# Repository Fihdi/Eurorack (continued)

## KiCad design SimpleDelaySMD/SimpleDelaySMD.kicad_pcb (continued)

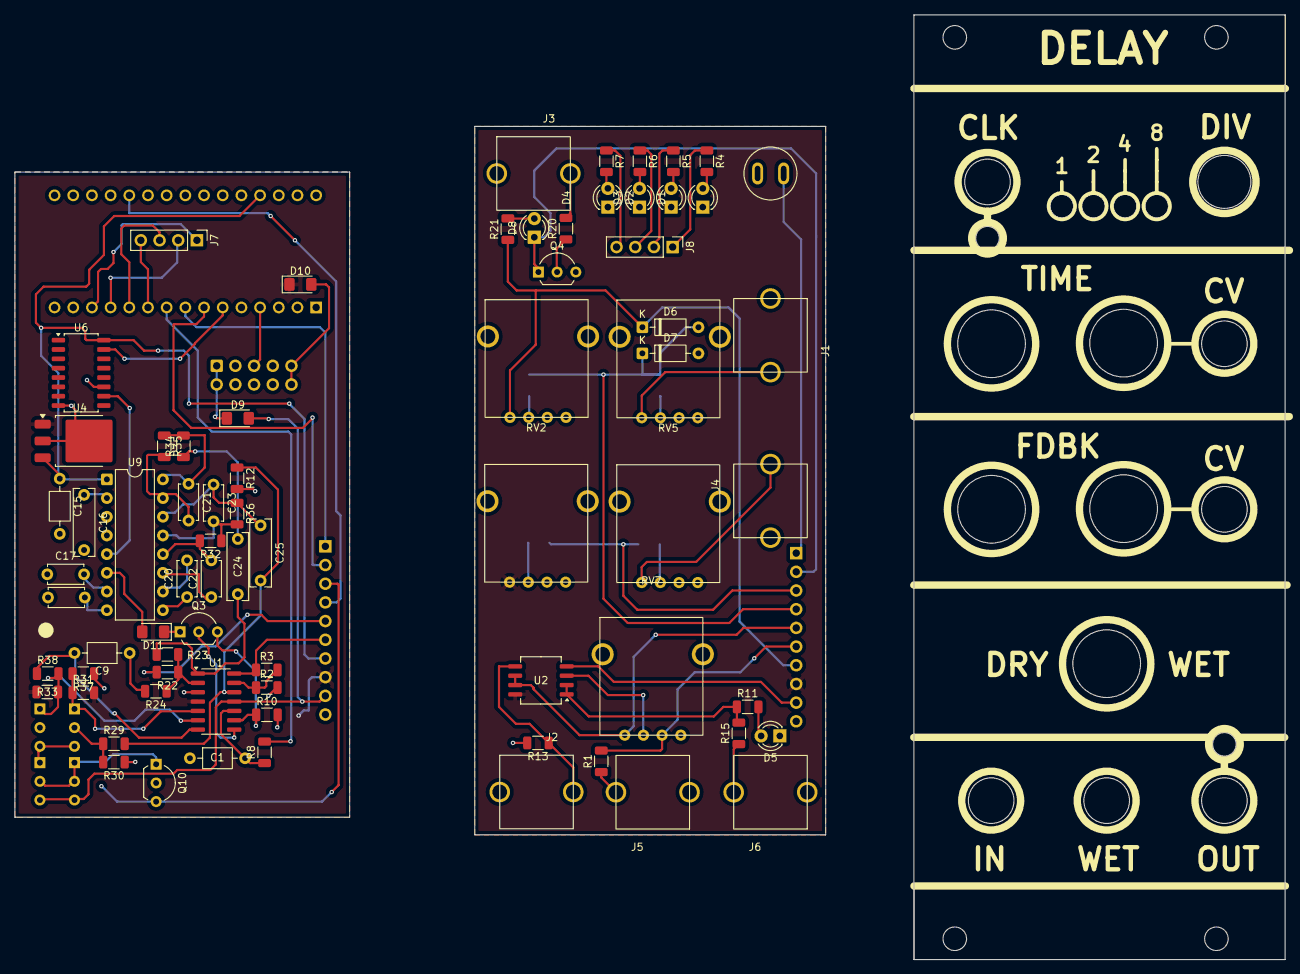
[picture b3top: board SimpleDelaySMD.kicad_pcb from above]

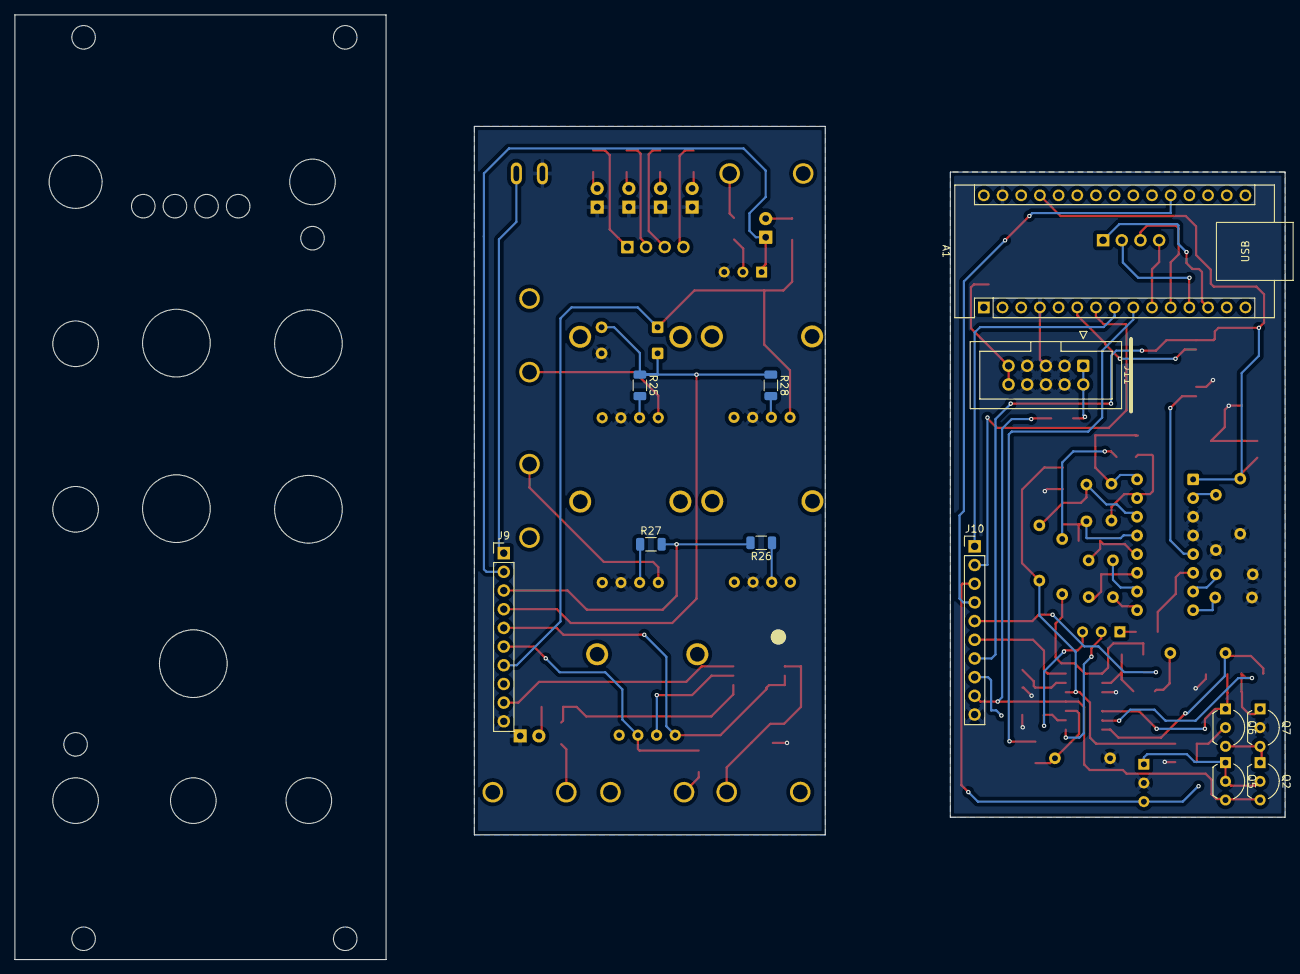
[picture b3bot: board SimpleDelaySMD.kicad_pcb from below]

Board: 2 copper layers, 172.6 x 128.4 mm, 85 parts (12 on the bottom side), 66 nets.

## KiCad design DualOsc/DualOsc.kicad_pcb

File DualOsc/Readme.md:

# 18hp Dual VCO module

Two triangle core VCOs with volt per octave tracking, FM, Synchronization and PWM. Both VCOs are identical and can be used independantely. The middle section allows for modulation (AM, FM and synchronization) from the left VCO to the right VCO and can be switched on or off via switches. The strength of this modulation is controllable via the AMT knob and a control voltage and is indicated by the arrow LED. Four trimmers at the back of the mainboard are used to tune the volt per octave responses and the sine shapers. 

This module was meant to replace my old VCO and I have decided to build this project using SMD components to save space and to test the in-house PCB assembly by [PCBWay](https://www.pcbway.com/). It was great to receive a fully assembled board without having to solder it for hours, which can be very tedious when using SMD components. The soldering was perfect out of the box and it allowed me to solder in the last THT components and to tune the module. The front panel is also made of FR4 with white silkscreen and a glossy black finish. I received great help from their support regarding the formatting of the BOM, which they used to source the materials and to assemble my PCB.

Here is a small demo: https://youtu.be/suYPOwo4L5c

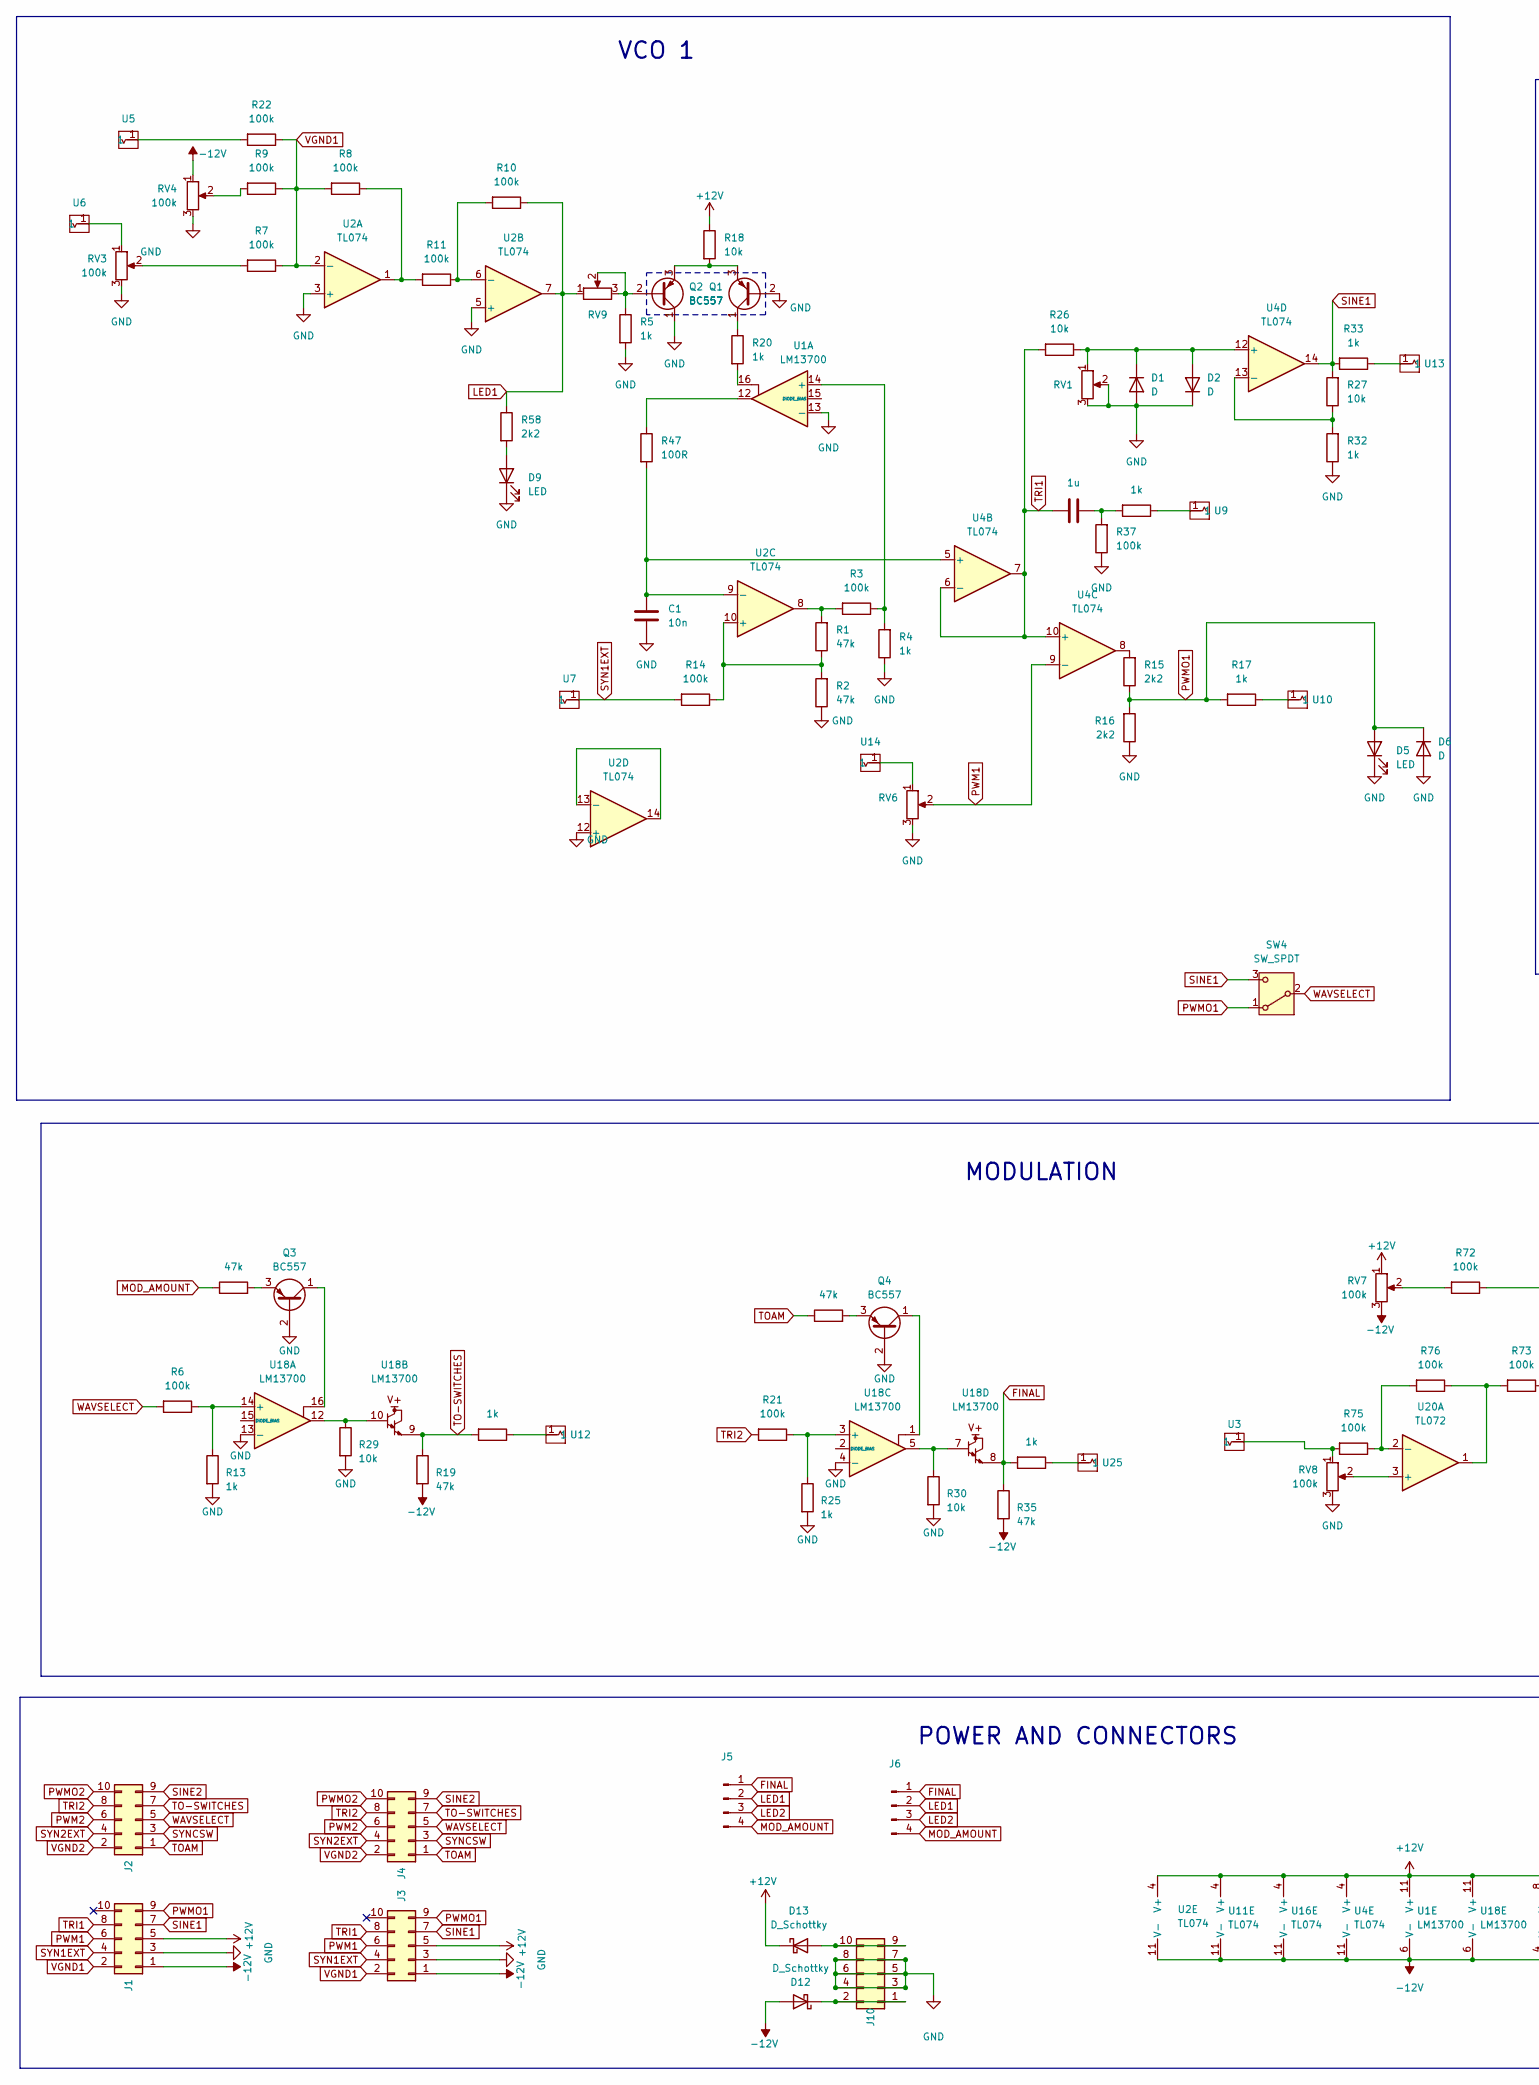
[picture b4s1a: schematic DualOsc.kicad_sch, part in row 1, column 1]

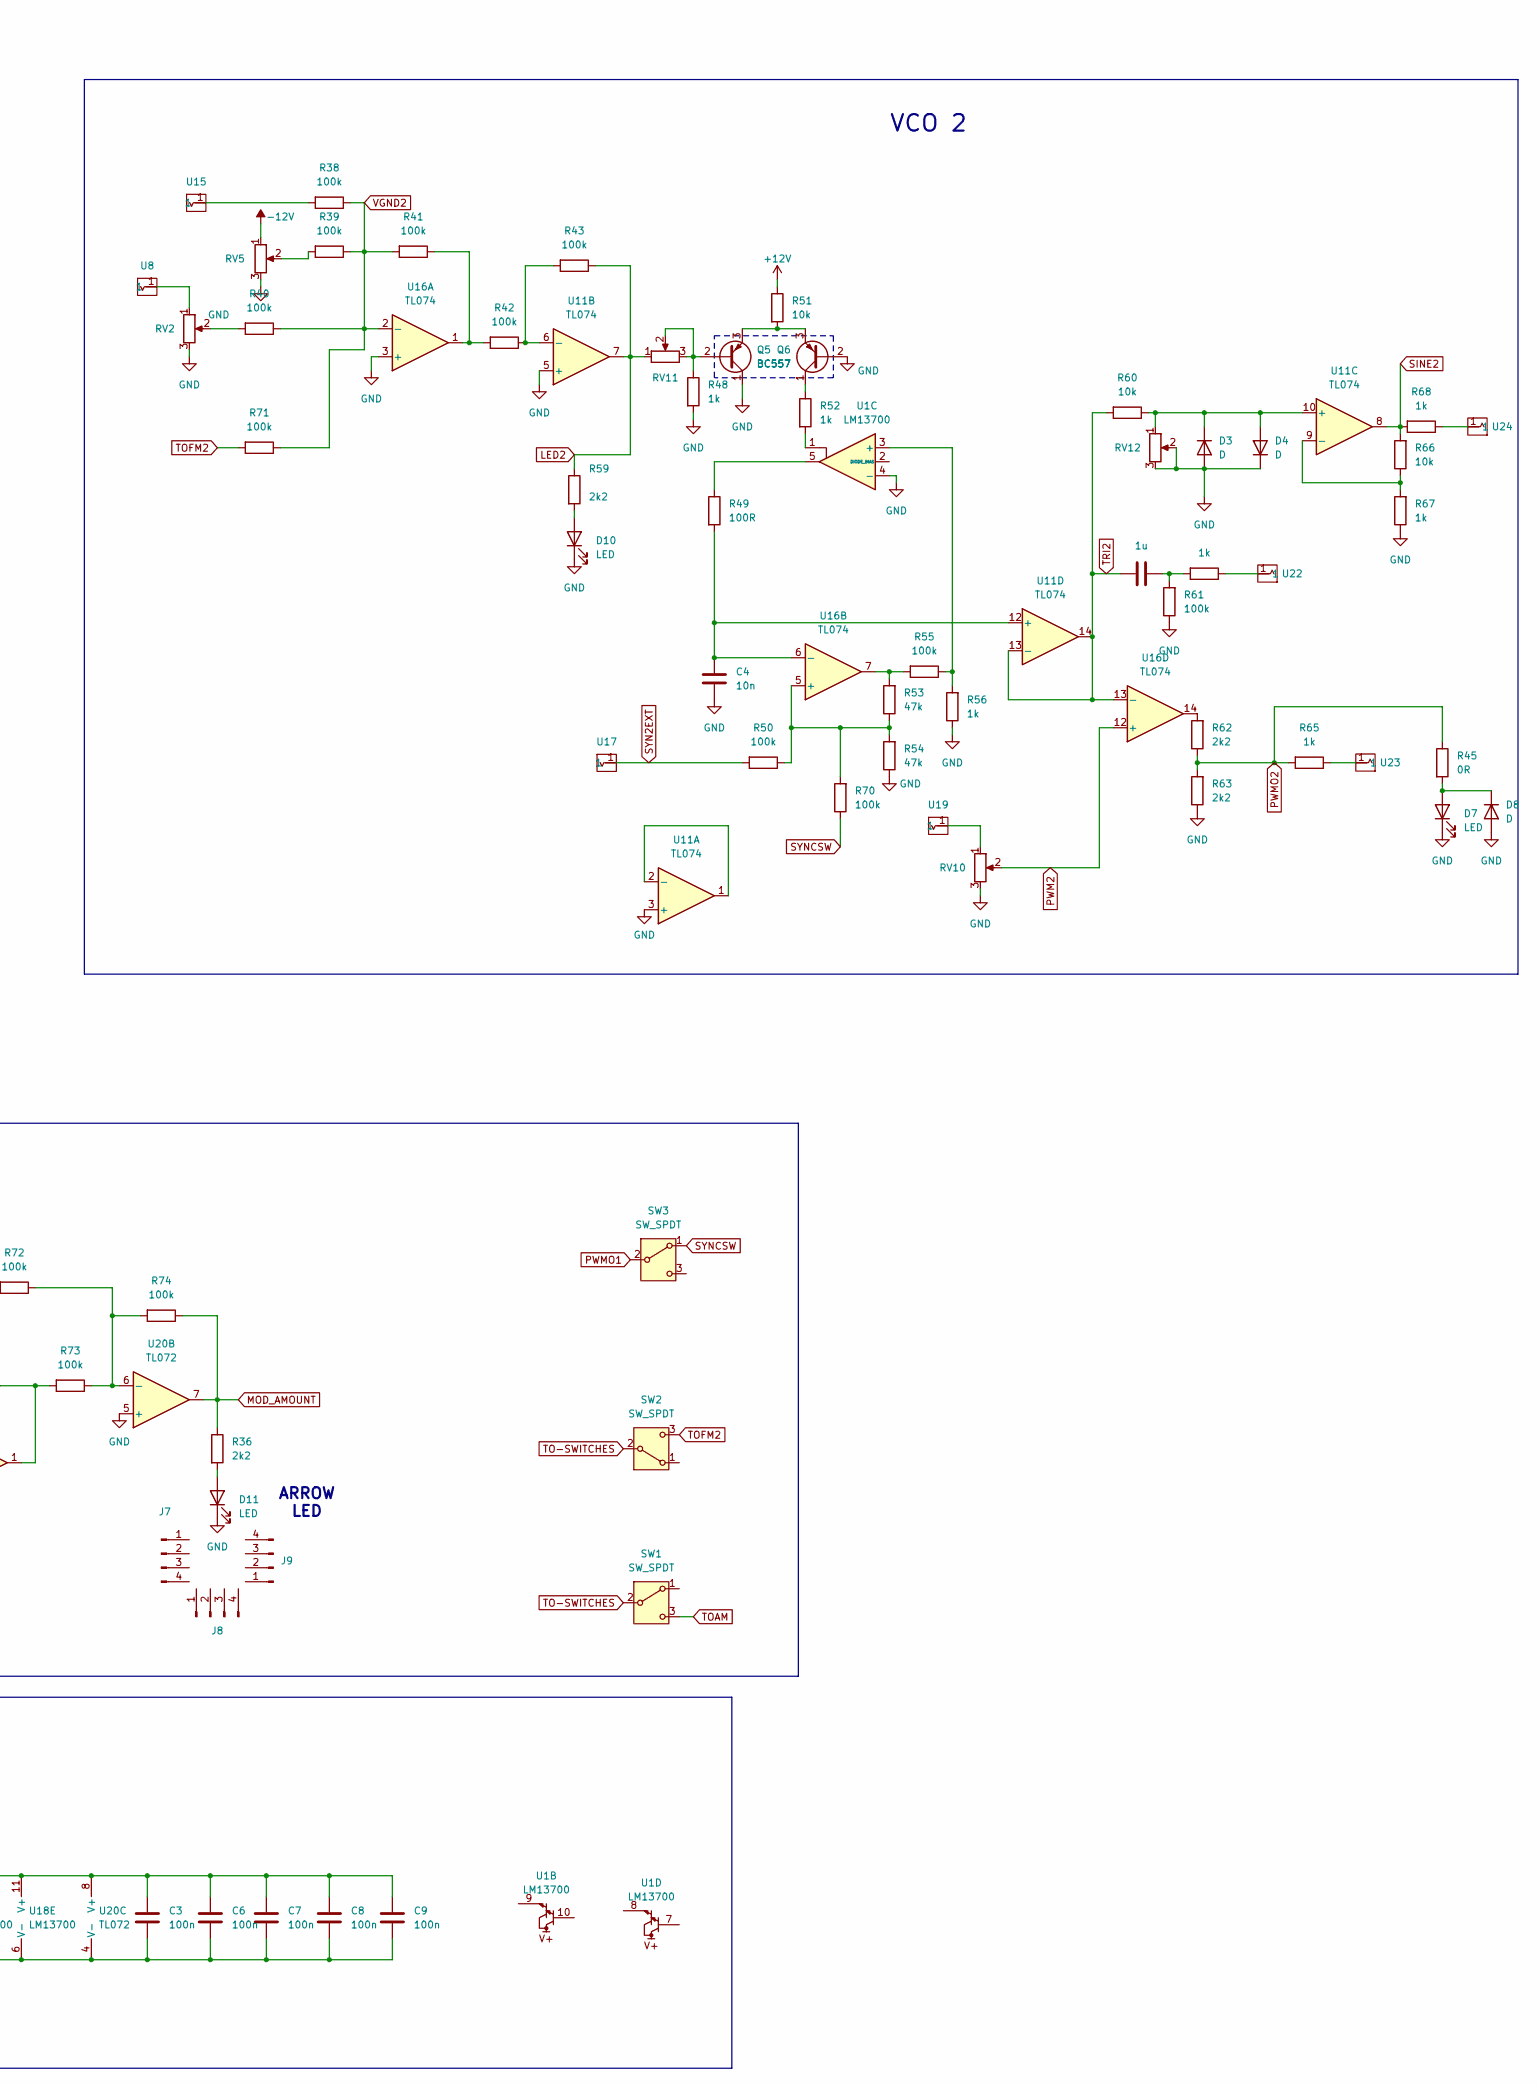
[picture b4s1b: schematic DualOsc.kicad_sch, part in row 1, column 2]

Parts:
C1, C4: 10n; C_Rect_L7.0mm_W2.5mm_P5.00mm
C2, C5: 1u; C_Rect_L7.0mm_W2.5mm_P5.00mm
C3, C6, C7, C8, C9: 100n; C_1206_3216Metric
D1, D2, D3, D4, D6, D8: D; D_SOD-323_HandSoldering
D5, D7, D9, D10, D11: LED; LED_D3.0mm
D12, D13: D_Schottky; D_SOD-323_HandSoldering
J1, J2, J3, J4: Conn_02x05_Odd_Even; PinHeader_2x05_P2.54mm_Vertical
J5, J6, J7, J8, J9: Conn_01x04_Pin; PinSocket_1x04_P2.54mm_Vertical
J10: Conn_02x05_Odd_Even; IDC-Header_2x05_P2.54mm_Vertical
Q1, Q2, Q3, Q4, Q5, Q6: BC557; TO-92L_Inline_Wide
R1, R2, R19, R28, R35, R53, R54, R83: 47k; R_1206_3216Metric
R3, R6, R7, R8, R9, R10, R11, R14, R21, R22, R37, R38, R39, R40, R41, R42, R43, R50, R55, R61, R70, R71, R72, R73, R74, R75, R76: 100k; R_1206_3216Metric
R4, R5, R12, R13, R17, R20, R25, R31, R32, R33, R48, R52, R56, R64, R65, R67, R68, R69: 1k; R_1206_3216Metric
R15, R16, R36, R58, R59, R62, R63: 2k2; R_1206_3216Metric
R18, R26, R27, R29, R30, R51, R60, R66: 10k; R_1206_3216Metric
R45: 0R; R_1206_3216Metric
R47, R49: 100R; R_1206_3216Metric
RV1, RV12: 4k7; Potentiometer_ACP_CA9-H5_Horizontal
RV2, RV3, RV4, RV5, RV7, RV8, RV10: 100k; AlpsPot
RV6: R_Potentiometer; AlpsPot
RV9, RV11: 47k; Potentiometer_ACP_CA9-H5_Horizontal
SW1, SW2, SW3, SW4: SW_SPDT; Switch
U1, U18: LM13700; SOIC-16_3.9x9.9mm_P1.27mm
U2, U4, U11, U16: TL074; SOIC-14_3.9x8.7mm_P1.27mm
U3, U5, U6, U7, U8, U9, U10, U12, U13, U14, U15, U17, U19, U22, U23, U24, U25: Aux_flush; 3mm5 Mono Aux
U20: TL072; SOIC-8_3.9x4.9mm_P1.27mm

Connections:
+12V: C3.1, C6.1, C7.1, C8.1, C9.1, D13.1 (K), J1.5, J3.5, R18.1, R51.1, RV7.1, U1.11 (V+), U2.4 (V+), U4.4 (V+), U11.4 (V+), U16.4 (V+), U18.11 (V+), U20.8 (V+)
-12V: C3.2, C6.2, C7.2, C8.2, C9.2, D12.2 (A), J1.1, J3.1, R19.2, R35.2, RV4.1, RV5.1, RV7.3, U1.6 (V-), U2.11 (V-), U4.11 (V-), U11.11 (V-), U16.11 (V-), U18.6 (V-), U20.4 (V-)
FINAL: J5.1, J6.1, R35.1, R69.2, U18.8
GND: C1.2, C4.2, D1.2 (A), D2.1 (K), D3.2 (A), D4.1 (K), D5.1 (K), D6.2 (A), D7.1 (K), D8.2 (A), D9.1 (K), D10.1 (K), D11.1 (K), J1.3, J3.3, J10.3, J10.4, J10.5, J10.6, J10.7, J10.8, Q1.2 (B), Q2.1 (C), Q3.2 (B), Q4.2 (B), Q5.1 (C), Q6.2 (B), R2.1, R4.1, R5.2, R13.2, R16.1, R25.2, R29.2, R30.2, R32.1, R37.1, R48.2, R54.1, R56.1, R61.1, R63.1, R67.1, RV1.2, RV1.3, RV2.3, RV3.3, RV4.3, RV5.3, RV6.3, RV8.3, RV10.3, RV12.2, RV12.3, U1.4 (-), U1.13 (-), U2.3 (+), U2.5 (+), U2.12 (+), U11.3 (+), U11.5 (+), U16.3 (+), U18.4 (-), U18.13 (-), U20.5 (+)
LED1: J5.2, J6.2, R10.1, R58.1, RV9.1, U2.7
LED2: J5.3, J6.3, R43.1, R59.1, RV11.1, U11.7
MOD_AMOUNT: J5.4, J6.4, R36.1, R74.1, R83.1, U20.7
unnamed: C2.2, R12.2, R37.2
unnamed: C5.2, R61.2, R64.2
unnamed: D1.1 (K), D2.2 (A), R26.1, RV1.1, U4.12 (+)
unnamed: D3.1 (K), D4.2 (A), R60.1, RV12.1, U11.10 (+)
unnamed: D7.2 (A), D8.1 (K), R45.2
unnamed: D9.2 (A), R58.2
unnamed: D10.2 (A), R59.2
unnamed: D11.2 (A), R36.2
unnamed: D12.1 (K), J10.1, J10.2
unnamed: D13.2 (A), J10.9, J10.10
unnamed: Q1.1 (C), R20.1
unnamed: Q1.3 (E), Q2.3 (E), R18.2
unnamed: Q2.2 (B), R5.1, RV9.2, RV9.3
unnamed: Q3.1 (C), U18.16
unnamed: Q3.3 (E), R83.2
unnamed: Q4.1 (C), U18.1
unnamed: Q4.3 (E), R28.2
unnamed: Q5.2 (B), R48.1, RV11.2, RV11.3
unnamed: Q5.3 (E), Q6.3 (E), R51.2
unnamed: Q6.1 (C), R52.1
unnamed: R1.2, R3.2, U2.8
unnamed: R7.2, RV3.2
unnamed: R9.2, RV4.2
unnamed: R8.1, R11.2, U2.1
unnamed: R12.1, U9.1
unnamed: R15.2, U4.8
unnamed: R17.1, U10.1
unnamed: R20.2, U1.16
unnamed: R22.2, U5.1
unnamed: R29.1, U18.10, U18.12
unnamed: R30.1, U18.5, U18.7
unnamed: R31.1, U12.1
unnamed: R33.1, U13.1
unnamed: R38.2, U15.1
unnamed: R39.2, RV5.2
unnamed: R40.2, RV2.2
unnamed: R41.1, R42.2, U16.1
unnamed: R47.1, U1.12
unnamed: R49.1, U1.5
unnamed: R52.2, U1.1
unnamed: R53.2, R55.2, U16.7
unnamed: R62.2, U16.14
unnamed: R64.1, U22.1
unnamed: R65.1, U23.1
unnamed: R68.1, U24.1
unnamed: R69.1, U25.1
unnamed: R72.2, RV7.2
unnamed: R73.2, R76.1, U20.1
unnamed: R75.2, RV8.1, U3.1
unnamed: RV2.1, U8.1
unnamed: RV3.1, U6.1
unnamed: RV6.1, U14.1
unnamed: RV10.1, U19.1
unnamed: R3.1, R4.2, U1.14 (+)
unnamed: R55.1, R56.2, U1.3 (+)
unnamed: R10.2, R11.1, U2.6 (-)
unnamed: R1.1, R2.2, R14.1, U2.10 (+)
unnamed: C1.1, R47.2, U2.9 (-), U4.5 (+)
unnamed: U2.13 (-), U2.14
unnamed: R27.1, R32.2, U4.13 (-)
unnamed: U11.1, U11.2 (-)
unnamed: R42.1, R43.2, U11.6 (-)
unnamed: R66.1, R67.2, U11.9 (-)
unnamed: C4.1, R49.2, U11.12 (+), U16.6 (-)
unnamed: R50.1, R53.1, R54.2, R70.2, U16.5 (+)
unnamed: R6.1, R13.1, U18.14 (+)
unnamed: R21.1, R25.1, U18.3 (+)
unnamed: RV8.2, U20.3 (+)
unnamed: R75.1, R76.2, U20.2 (-)
unnamed: R72.1, R73.1, R74.2, U20.6 (-)
PWM1: J1.6, J3.6, RV6.2, U4.9 (-)
PWM2: J2.6, J4.6, RV10.2, U16.12 (+)
PWMO1: D5.2 (A), D6.1 (K), J1.9, J3.9, R15.1, R16.2, R17.2, SW3.2 (B), SW4.1 (A)
PWMO2: J2.10, J4.10, R45.1, R62.1, R63.2, R65.2
SINE1: J1.7, J3.7, R27.2, R33.2, SW4.3 (C), U4.14
SINE2: J2.9, J4.9, R66.2, R68.2, U11.8
SYN1EXT: J1.4, J3.4, R14.2, U7.1
SYN2EXT: J2.4, J4.4, R50.2, U17.1
SYNCSW: J2.3, J4.3, R70.1, SW3.1 (A)
TO-SWITCHES: J2.7, J4.7, R19.1, R31.2, SW1.2 (B), SW2.2 (B), U18.9
TOAM: J2.1, J4.1, R28.1, SW1.3 (C)
TOFM2: R71.2, SW2.3 (C)
TRI1: C2.1, J1.8, J3.8, R26.2, U4.6 (-), U4.7, U4.10 (+)
TRI2: C5.1, J2.8, J4.8, R21.2, R60.2, U11.13 (-), U11.14, U16.13 (-)
VGND1: J1.2, J3.2, R7.1, R8.2, R9.1, R22.1, U2.2 (-)
VGND2: J2.2, J4.2, R38.1, R39.1, R40.1, R41.2, R71.1, U16.2 (-)
WAVSELECT: J2.5, J4.5, R6.2, SW4.2 (B)

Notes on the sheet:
MODULATION
VCO 1
ARROW LED
POWER AND CONNECTORS
VCO 2

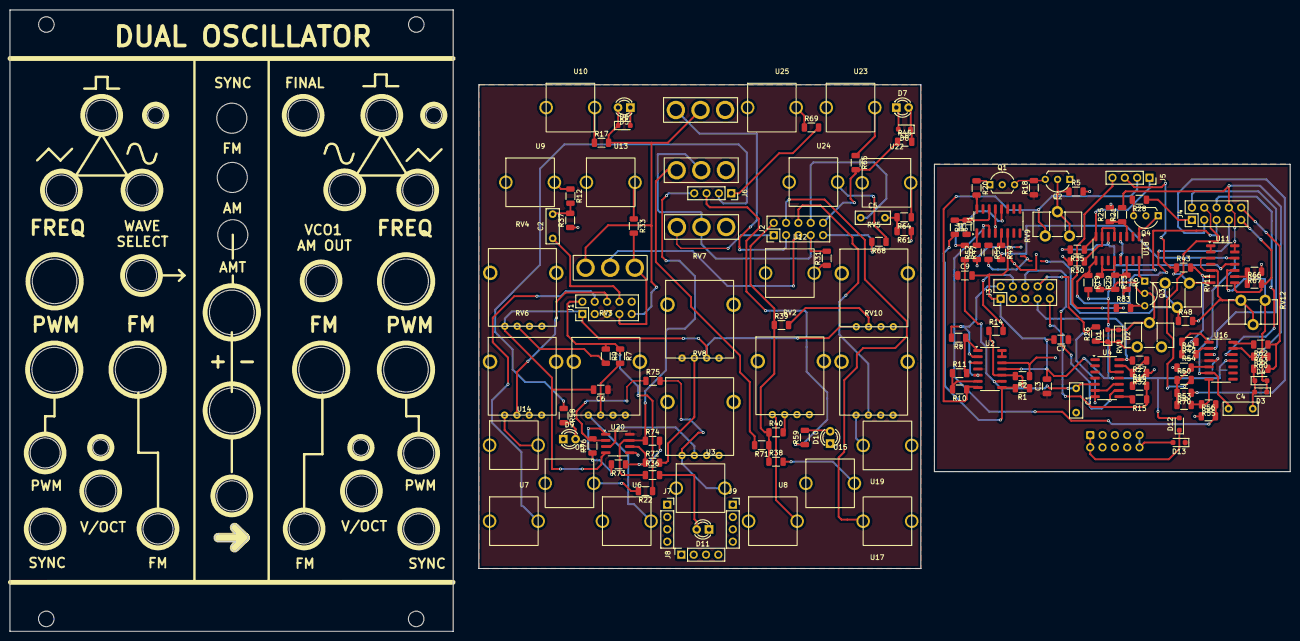
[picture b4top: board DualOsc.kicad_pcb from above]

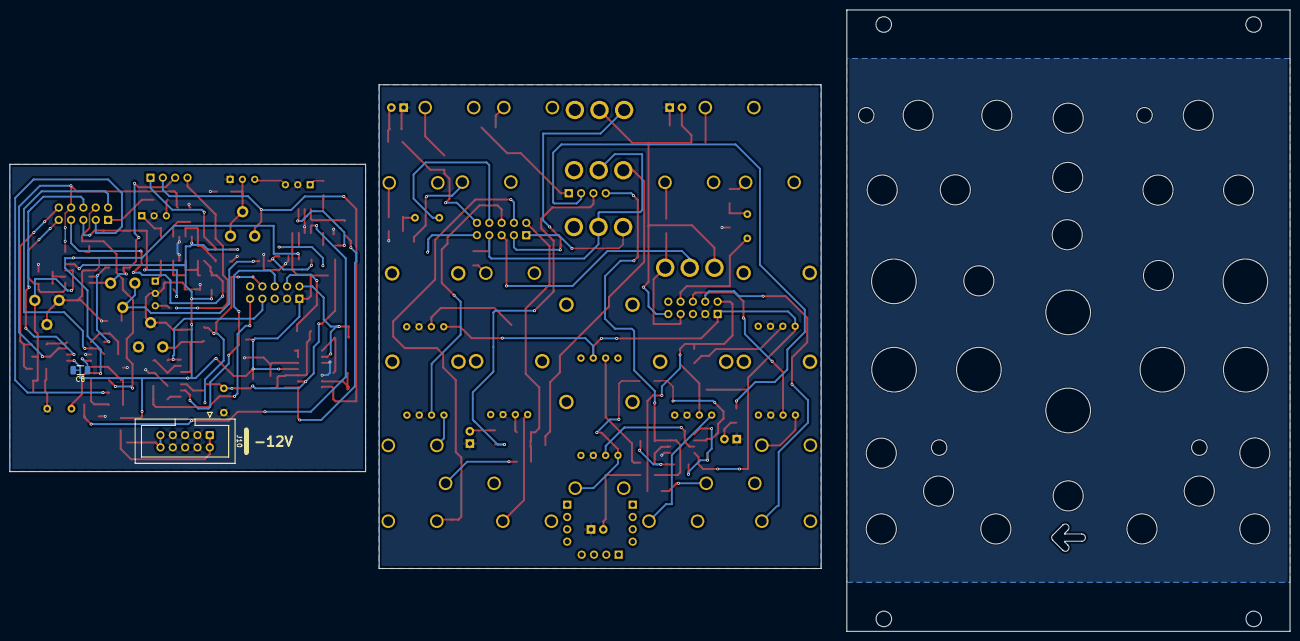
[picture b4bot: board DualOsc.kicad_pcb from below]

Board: 2 copper layers, 263.7 x 128.0 mm, 147 parts (2 on the bottom side), 92 nets.

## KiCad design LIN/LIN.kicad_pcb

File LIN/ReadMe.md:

# 4hp Line Input / VCA 

LIN is a 4hp Line Input module allowing you to take a line level signal from eg. a laptop, mp3 player, mobile phone etc. and boost it to Eurorack level. The volume is controlled by a VCA, which allows you to control the volume, or chop up the incoming audio signal. You can also distort existing eurorack signal by boosting the signal until it clips.

The module that you see in the picture above is the finished product using circuit boards that were fabricated by PCBWay. It is my smallest (slimmest) module so far and as always, they have excellent build quality! I used the "Black" option for the soldermask and the surface has very deep and glossy black finish, which looks amazing.

[Visit PCBWay](https://www.pcbway.com/) The website is intuitive and easy to use, just upload the gerber and drill files as a .zip-file, tick the options such as base material, board width, my favorite feature: separate colors for the soldermask and silkscreen, surface finish etc. With multiple options for payment and fast delivery fast times I was able to put the entire project together in less than one month.

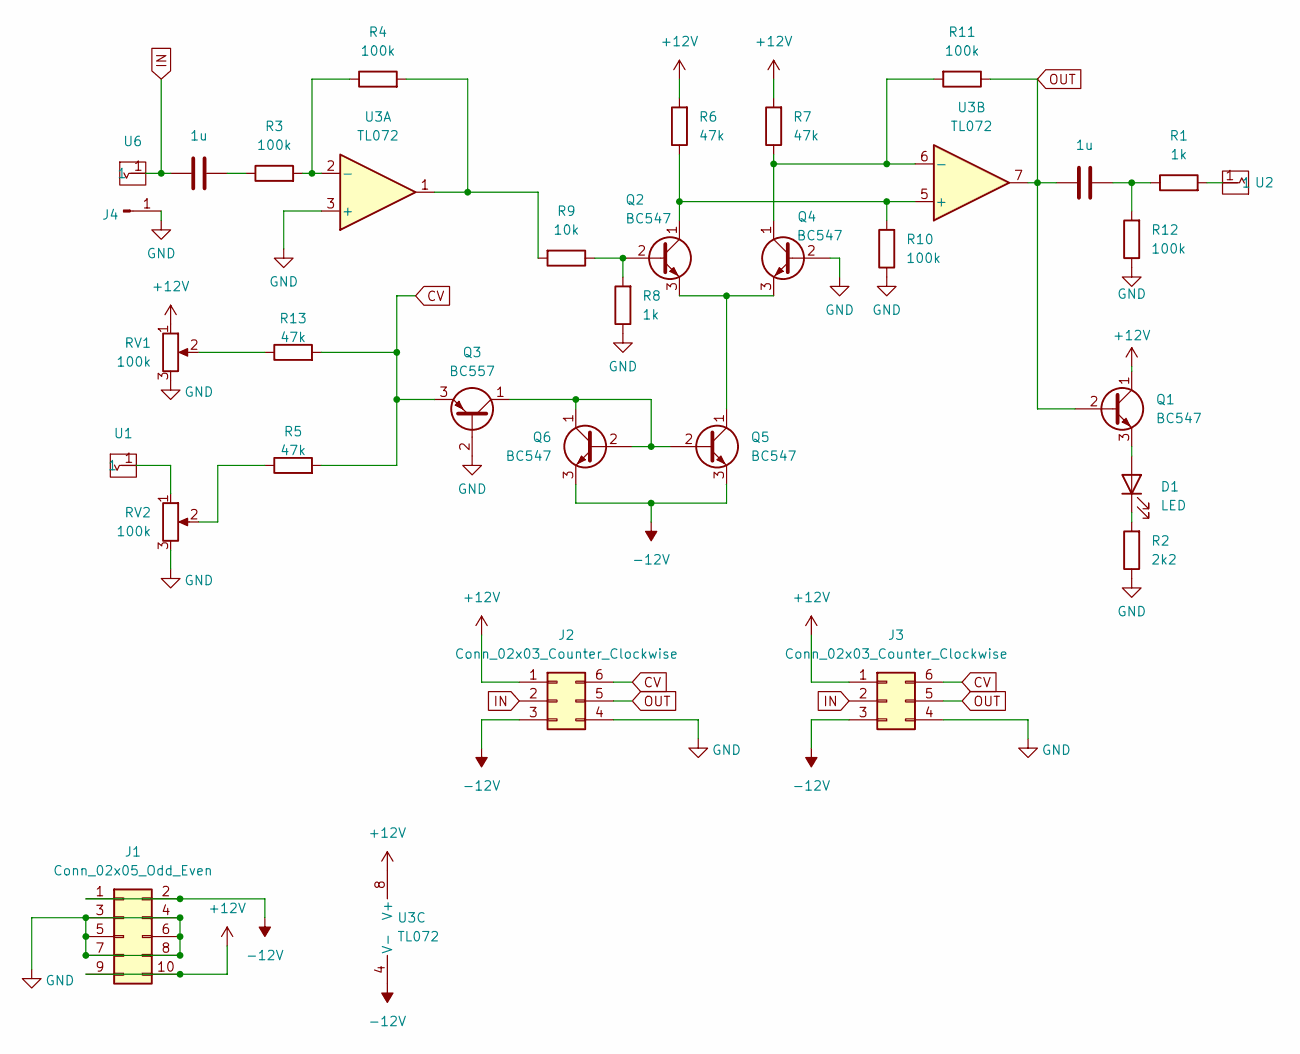
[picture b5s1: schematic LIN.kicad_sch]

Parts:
C1, C9: 1u; C_Axial_L3.8mm_D2.6mm_P7.50mm_Horizontal
D1: LED; LED_D5.0mm
J1: Conn_02x05_Odd_Even; IDC-Header_2x05_P2.54mm_Vertical
J2, J3: Conn_02x03_Counter_Clockwise; PinHeader_2x03_P2.54mm_Vertical
J4: Conn_01x01_Pin; PinSocket_1x01_P2.54mm_Vertical
Q1, Q2, Q4, Q5, Q6: BC547; TO-92L_Wide
Q3: BC557; TO-92L_Inline_Wide
R1, R8: 1k; R_Axial_DIN0207_L6.3mm_D2.5mm_P7.62mm_Horizontal
R2: 2k2; R_Axial_DIN0207_L6.3mm_D2.5mm_P7.62mm_Horizontal
R3, R4, R10, R11, R12: 100k; R_Axial_DIN0207_L6.3mm_D2.5mm_P7.62mm_Horizontal
R5, R6, R7, R13: 47k; R_Axial_DIN0207_L6.3mm_D2.5mm_P7.62mm_Horizontal
R9: 10k; R_Axial_DIN0207_L6.3mm_D2.5mm_P7.62mm_Horizontal
RV1, RV2: 100k; AlpsPot
U1, U2, U6: Aux_flush; 3mm5 Mono Aux
U3: TL072; DIP-8_W7.62mm

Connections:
+12V: J1.9, J1.10, J2.1, J3.1, Q1.1 (C), R6.2, R7.2, RV1.1, U3.8 (V+)
-12V: J1.1, J1.2, J2.3, J3.3, Q5.3 (E), Q6.3 (E), U3.4 (V-)
CV: J2.6, J3.6, Q3.3 (E), R5.2, R13.2
GND: J1.3, J1.4, J1.5, J1.6, J1.7, J1.8, J2.4, J3.4, J4.1, Q3.2 (B), Q4.2 (B), R2.1, R8.1, R10.1, R12.1, RV1.3, RV2.3, U3.3 (+)
IN: C1.2, J2.2, J3.2, U6.1
unnamed: C1.1, R3.1
unnamed: C9.1, R1.1, R12.2
unnamed: D1.2 (A), Q1.3 (E)
unnamed: D1.1 (K), R2.2
unnamed: Q2.2 (B), R8.2, R9.1
unnamed: Q2.1 (C), R6.1, R10.2, U3.5 (+)
unnamed: Q2.3 (E), Q4.3 (E), Q5.1 (C)
unnamed: Q3.1 (C), Q5.2 (B), Q6.1 (C), Q6.2 (B)
unnamed: Q4.1 (C), R7.1, R11.2, U3.6 (-)
unnamed: R1.2, U2.1
unnamed: R4.2, R9.2, U3.1
unnamed: R5.1, RV2.2
unnamed: R13.1, RV1.2
unnamed: RV2.1, U1.1
unnamed: R3.2, R4.1, U3.2 (-)
OUT: C9.2, J2.5, J3.5, Q1.2 (B), R11.1, U3.7

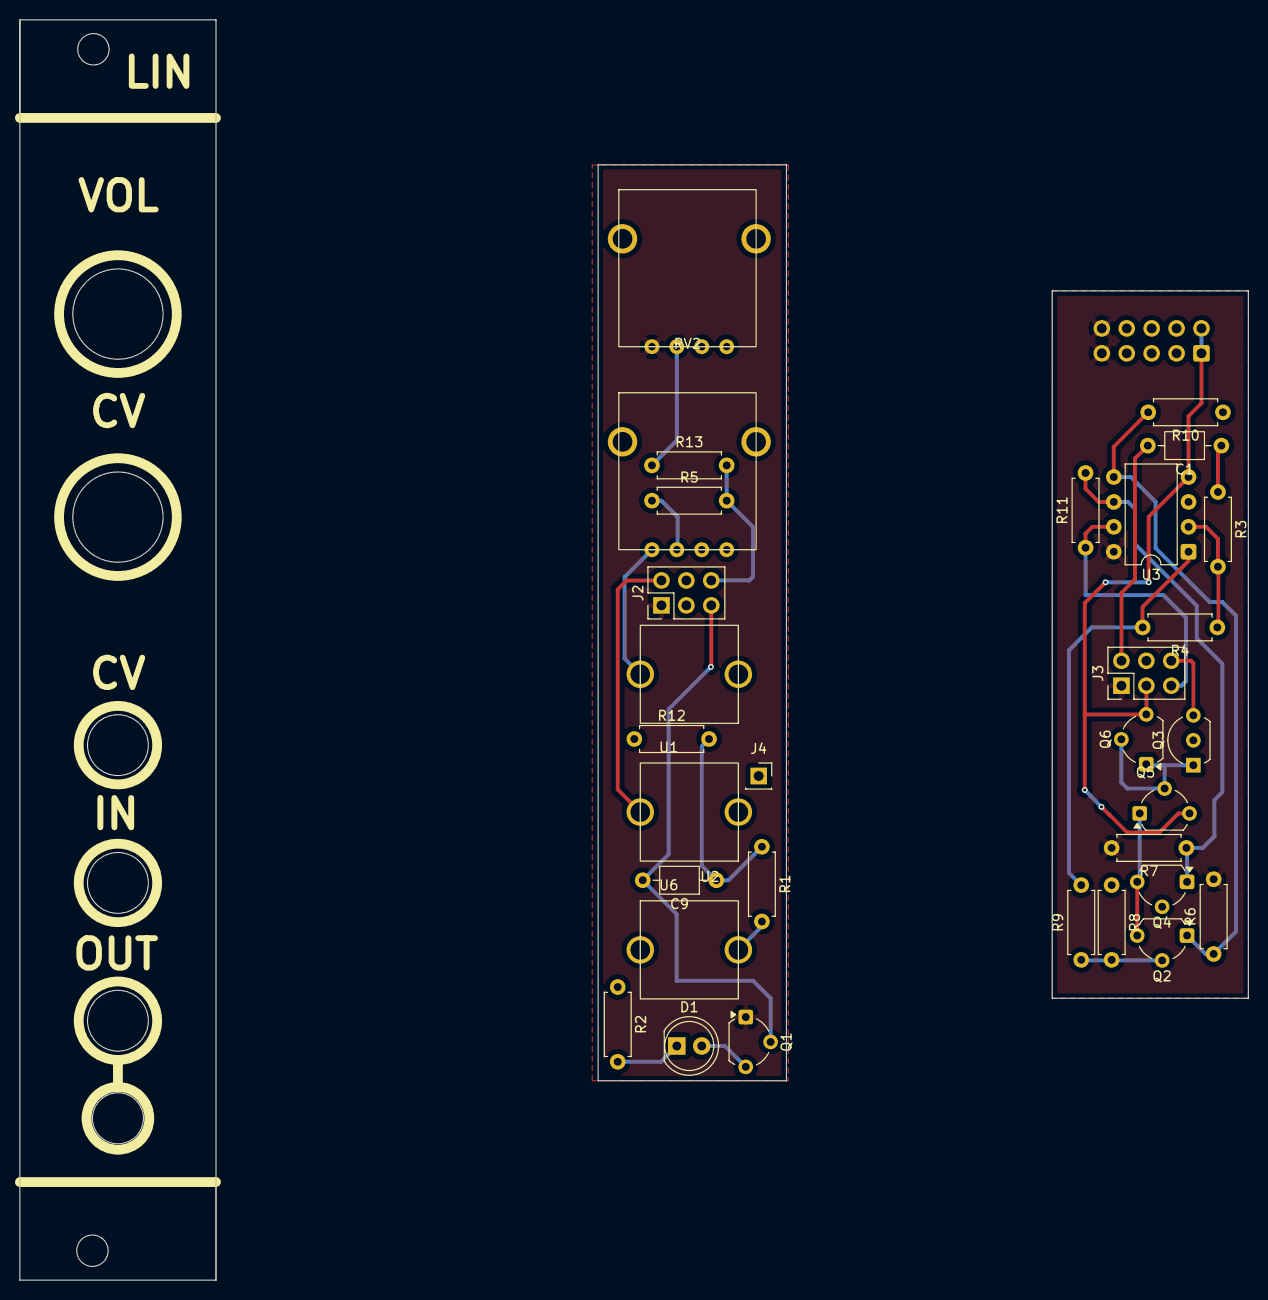
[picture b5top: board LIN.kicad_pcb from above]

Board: 2 copper layers, 125.3 x 128.5 mm, 32 parts (1 on the bottom side), 21 nets.

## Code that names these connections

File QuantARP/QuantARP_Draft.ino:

/*

Code by Fihdi

Matrix Keypad values:

13 = no key

col 1, 2, 3, 4
_________________
| 1 | 2 | 3 | 4 | row1 
_________________
| 5 | 6 | 7 | 8 | row2
_________________
| 9 | 10| 11| 12| row3
_________________

Scale:
col 1, 2, 3, 4
_________________
| C | C#| D | D#| row1 
_________________
| E | F | F#| G | row2
_________________
| G#| A | A#| B | row3
_________________

*/


#include "TCA9555.h"

#define TRG 9  //TRG Input Pin
#define CVIN A1   //CV Input Pin
#define ARP 5   //ARP Input Pin

#define CVOUT 10   //CV Output Pin
#define AUD 11  //Audio Output Pin

//Matrix Keypad Pins
#define ROW1 6
#define ROW2 7
#define ROW3 8
#define COL1 3
#define COL2 2
#define COL3 4
#define COL4 5

//LED Pins 
TCA9535 TCA(0x20);
#define LED1 1
#define LED2 2
#define LED3 3
#define LED4 4
#define LED5 5
#define LED6 6
#define LED7 7
#define LED8 8
#define LED9 9
#define LED10 10
#define LED11 11
#define LED12 12

int leds[12] = { LED1, LED2, LED3, LED4, LED5, LED6, LED7, LED8, LED9, LED10, LED11, LED12 };

int noteInOctave = 0;
int currentSemitone = 0; //currently played note
int lastquantized = 0;

//It takes (1023/5)*(1/12) = 17.05 bits to change one semitone, thus we can set the hysteresis to 14.
int hysteresis = 14;

bool scale[12] = {
  true,   // C
  false,  // C#
  true,   // D
  false,  // D#
  true,   // E
  true,   // F
  false,  // F#
  true,   // G
  false,  // G#
  true,   // A
  false,  // A#
  true    // B
};

int arpScale[24] = {};
int arpIndex = 0;      // current position in the arpeggio
int noteAmount = 0; //Amount of notes in the scales

volatile bool TRGInterrupted = false;
volatile bool TRGtriggered = false;

volatile bool ARPInterrupted = false;
volatile bool ARPtriggered = false;

volatile bool keypadInterrupted;

volatile int lastCV;

void setup() {
  Wire.begin();
  TCA.begin();
  Wire.setClock(50000);

//Increase PWM Frequency
  TCCR0A = 0b00000011;
  TCCR0B = 0b00000001;
  TCCR1A = 0b00000001;
  TCCR1B = 0b00001001;
  TCCR2A = 0b00000011;
  TCCR2B = 0b00000001;

  Serial.begin(9600);

  pinMode(ROW1, INPUT);
  pinMode(ROW2, INPUT);
  pinMode(ROW3, INPUT);

  pinMode(COL1, OUTPUT);
  pinMode(COL2, OUTPUT);
  pinMode(COL3, OUTPUT);
  pinMode(COL4, OUTPUT);

  pinMode(TRG, INPUT_PULLUP);
  pinMode(CVIN, INPUT);
  pinMode(CVOUT, OUTPUT);
  pinMode(AUD, OUTPUT);

  for (int i = 0; i < 12; i++) {
    TCA.pinMode1(leds[i], OUTPUT);
    TCA.write1(leds[i], HIGH);
    delay(700);
  }
  TCA.pinMode1(13, OUTPUT);
}

// Scale: true = note is allowed in the scale
// Index 0 = C, 1 = C#, ..., 11 = B

//find the nearest allowed semitone
int quantizeToScale(int semitone) {
  int octave = semitone / 12;
  noteInOctave = semitone % 12;
  // Serial.println(noteInOctave);

  // Search outward for closest allowed note in the scale
  for (int offset = 0; offset < 12; offset++) {
    // Check upward
    int up = (noteInOctave + offset) % 12;
    if (scale[up]) {
      //  lastquantized = octave * 12 + up;
      return octave * 12 + up;
    }
    // Check downward
    int down = (noteInOctave - offset + 12) % 12;
    if (scale[down]) {
      // lastquantized = octave * 12 + down;
      return octave * 12 + down;
    }
  }
  // Fallback: return unquantized semitone if no scale notes found (shouldn’t happen)
  return semitone;
}

void loop() {
checkKeypadTriggered();
checkInputCVChange();
checkTRG();
outputLeds();
delay(10);  // Optional smoothing delay
}
void checkInputCVChange(){
int raw = analogRead(CVIN);     // 0–1023
  //Only update the CV and AUD if the CV Input(Or offset knob) has changed
  if (((lastCV - raw) >= hysteresis)||((raw - lastCV) >= hysteresis)) {
    writeCVandAUD();
  }
}

void writeCVandAUD() {

  int raw = analogRead(CVIN);     // 0–1023

    float voltage = raw * (5.0 / 1023.0);
  // Convert to semitone number (0–60): 12 semitones per volt
  int semitone = round(voltage * 12.0);

    lastCV = raw;
    //value decreased
    currentSemitone = quantizeToScale(semitone);

  int frequency = 440 * pow(2.0, (currentSemitone - 49.0 - 4.0 /*offset for so the base tone is C*/) / 12.0);
  tone(AUD, (int)frequency);
  float quantizedVoltage = currentSemitone / 12.0;
  int pwmValue = map(quantizedVoltage * 100, 0, 500, 0, 255);
  pwmValue = constrain(pwmValue, 0, 255);
  analogWrite(CVOUT, pwmValue);
  
}

void outputLeds() {

  for (int i = 0; i < 12; i++) {
    if (scale[i]) {
      if( (currentSemitone % 12) != i){
        TCA.write1(leds[i], HIGH);  //Write LED HIGH if it is in the scale and NOT the current note being played.
      }else{
TCA.write1(leds[i], LOW);
      }
    }else{
      TCA.write1(leds[i], LOW);
    }
    
  }
}


int readMatrixKeypad() {
  //Check Column 1:
  digitalWrite(COL1, HIGH);
  digitalWrite(COL2, LOW);
  digitalWrite(COL3, LOW);
  digitalWrite(COL4, LOW);

  //Read in the rows
  if (digitalRead(ROW1) == 1) { /*1-1*/
    return 1;
  }
  if (digitalRead(ROW2) == 1) { /*1-2*/
    return 5;
  }
  if (digitalRead(ROW3) == 1) { /*1-3*/
    return 9;
  }
  //Check Column 2:
  digitalWrite(COL1, LOW);
  digitalWrite(COL2, HIGH);
  digitalWrite(COL3, LOW);
  digitalWrite(COL4, LOW);

  if (digitalRead(ROW1) == 1) { /*2-1*/
    return 2;
  }
  if (digitalRead(ROW2) == 1) { /*2-2*/
    return 6;
  }
  if (digitalRead(ROW3) == 1) { /*2-3*/
    return 10;
  }

  //Check Column 3:
  digitalWrite(COL1, LOW);
  digitalWrite(COL2, LOW);
  digitalWrite(COL3, HIGH);
  digitalWrite(COL4, LOW);

  if (digitalRead(ROW1) == 1) { /*3-1*/
    return 3;
  }
  if (digitalRead(ROW2) == 1) { /*3-2*/
    return 7;
  }
  if (digitalRead(ROW3) == 1) { /*3-3*/
    return 11;
  }

  //Check Column 4:
  digitalWrite(COL1, LOW);
  digitalWrite(COL2, LOW);
  digitalWrite(COL3, LOW);
  digitalWrite(COL4, HIGH);

  if (digitalRead(ROW1) == 1) { /*4-1*/
    return 4;
  }
  if (digitalRead(ROW2) == 1) { /*4-2*/
    return 8;
  }
  if (digitalRead(ROW3) == 1) { /*4-3*/
    return 12;
  }

  //No key pressed
  return 13;
}

void checkKeypadTriggered() {
  int keypad = readMatrixKeypad();

  bool keypadtriggered = (keypad != 13) && (keypadInterrupted == false); //A key was pressed AND we are not in the ISR yet 

  if (keypadtriggered) {
    Serial.println(keypad);
    keypadInterrupted = true;

    scale[keypad-1] = !scale[keypad-1];  //Invert the state for the pressed key.
    if(countNotes() == 0){
      scale[keypad-1] = !scale[keypad-1];  //Undo the Inverting if it resulted in all of the notes being off.
    }
    
  }

  if ((keypad == 13) && (keypadInterrupted == true)) {
    keypadInterrupted = false;  //Reset  flag
  }
}

void readARP() {
}

//Count the number of active keys in the scale
int countNotes(){
  int count = 0;
  for (int i = 0; i < 12; i++) {
    if(scale[i]){
      count++;
    }
 }
 return count;
}

void checkTRG() {

  TRGtriggered = (digitalRead(TRG) == LOW) && (TRGInterrupted == false);

  if (TRGtriggered) {
    //Triggered!
    TRGInterrupted = true;
    
    buildARPScale();

    int currentOctave = currentSemitone/12;

    arpIndex = (arpIndex + 1) % noteAmount; //Increase/Cycle the index for the amount of notes in the scale
    
    currentSemitone = currentOctave*12 + arpScale[arpIndex];
    //OUTPUT CV and AUDIO
    int frequency = 440 * pow(2.0, (currentSemitone - 49.0 - 4.0 /*offset for so the base tone is C*/) / 12.0);
  tone(AUD, (int)frequency);
  float quantizedVoltage = currentSemitone / 12.0;
  int pwmValue = map(quantizedVoltage * 100, 0, 500, 0, 255);
  pwmValue = constrain(pwmValue, 0, 255);
  analogWrite(CVOUT, pwmValue);
    
    outputLeds();
  }

  if ((digitalRead(TRG) == HIGH) && (TRGInterrupted == true)) {
    TRGInterrupted = false;  //Reset trigger flag
  }
}

void buildARPScale(){

//Builds an array of "offsets" used for the Arpeggiator
//Example: the indexes for C major are (starting at 0): 0, 2, 4, 5, 7, 9, 11,
//Using this array, we jump to the first note in the scale in the active octave and then output: currentoctave + offset
noteAmount = 0;
for (int i = 0; i < 12; i++) {
  if(scale[i]){
    arpScale[noteAmount] = i;
    noteAmount++;
  }
}
}
